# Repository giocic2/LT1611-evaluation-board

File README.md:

# LT1611-evaluation-board
Inverting voltage regulator

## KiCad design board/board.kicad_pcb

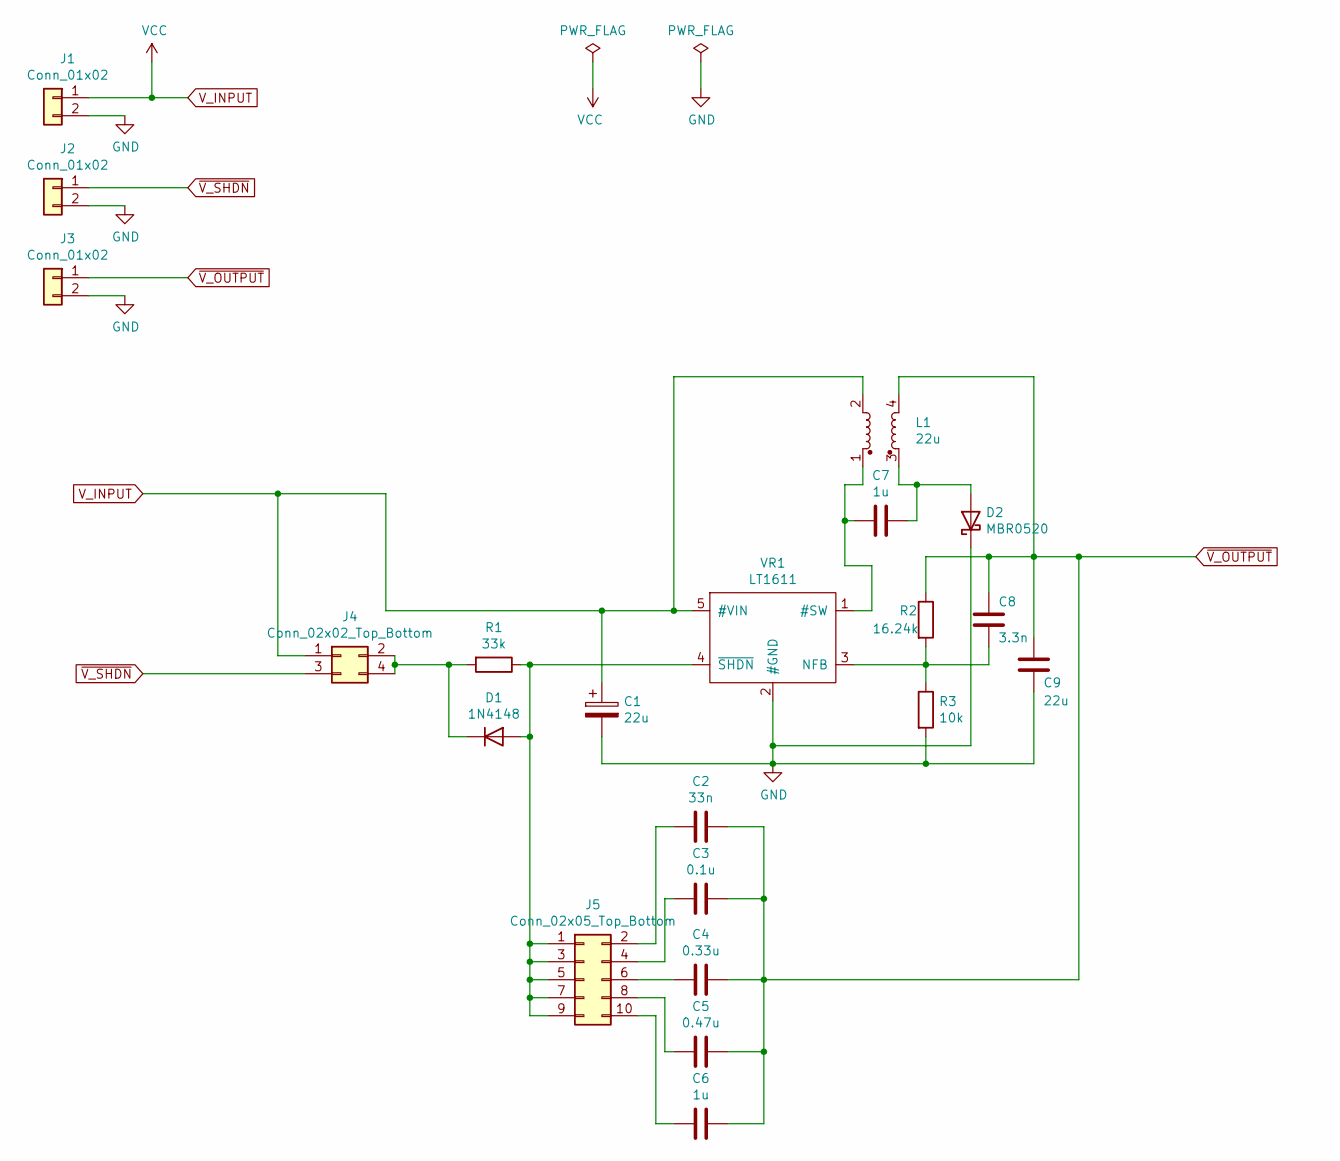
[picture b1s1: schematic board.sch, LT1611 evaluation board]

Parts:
C1: 22u; CP_Elec_4x5.8
C2: 33n; C_0603_1608Metric_Pad1.08x0.95mm_HandSolder
C3: 0.1u; C_0603_1608Metric_Pad1.08x0.95mm_HandSolder
C4: 0.33u; C_0603_1608Metric_Pad1.08x0.95mm_HandSolder
C5: 0.47u; C_0603_1608Metric_Pad1.08x0.95mm_HandSolder
C6, C7: 1u; C_0603_1608Metric_Pad1.08x0.95mm_HandSolder
C8: 3.3n; C_0603_1608Metric_Pad1.08x0.95mm_HandSolder
C9: 22u; C_1210_3225Metric_Pad1.33x2.70mm_HandSolder
D1: 1N4148; D_SOD-523
D2: MBR0520; D_SOD-123
J1, J2, J3: Conn_01x02; PinHeader_1x02_P2.54mm_Vertical
J4: Conn_02x02_Top_Bottom; PinHeader_2x02_P2.54mm_Vertical
J5: Conn_02x05_Top_Bottom; PinHeader_2x05_P2.54mm_Vertical
L1: 22u; L_coupled_WE_MCRI
R1: 33k; R_0603_1608Metric_Pad0.98x0.95mm_HandSolder
R2: 16.24k; R_0603_1608Metric_Pad0.98x0.95mm_HandSolder
R3: 10k; R_0603_1608Metric_Pad0.98x0.95mm_HandSolder
VR1: LT1611; SOT-23-5_HandSoldering

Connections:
GND: C1.2, C9.1, D2.1 (K), J1.2, J2.2, J3.2, R3.2, VR1.2 (#GND)
unnamed: C2.2, J5.2
unnamed: C3.2, J5.4
unnamed: C4.2, J5.6
unnamed: C5.2, J5.8
unnamed: C6.2, J5.10
unnamed: C7.1, D2.2 (A), L1.3
unnamed: C7.2, L1.1, VR1.1 (#SW)
unnamed: C8.2, R2.2, R3.1, VR1.3 (NFB)
unnamed: D1.1 (K), J4.2, J4.4, R1.2
unnamed: D1.2 (A), J5.1, J5.3, J5.5, J5.7, J5.9, R1.1, VR1.4 (~SHDN)
V_INPUT: C1.1, J1.1, J4.1, L1.2, VR1.5 (#VIN)
~V_OUTPUT: C2.1, C3.1, C4.1, C5.1, C6.1, C8.1, C9.2, J3.1, L1.4, R2.1
~V_SHDN: J2.1, J4.3

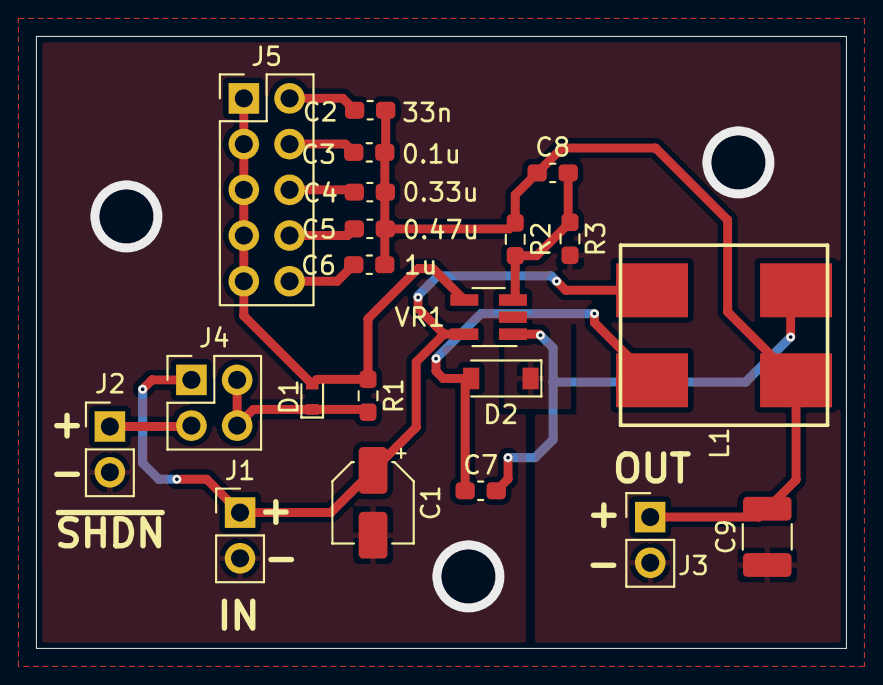
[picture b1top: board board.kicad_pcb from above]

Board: 2 copper layers, 45.0 x 34.0 mm, 21 parts (0 on the bottom side), 14 nets.

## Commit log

2021-08-17 schematic completed
2021-08-18 pcb layout completed
2021-09-16 minor changes i guess
2021-10-06 gerber files generated
2021-10-08 BOM with corrections for out-of-stock components
2021-10-08 Gerber files
